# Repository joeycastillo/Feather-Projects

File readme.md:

# Joey's Feather Projects

Finally figured I'd get my hardware hacking efforts under version control. All of these boards are designed to validate under OSH Park's design rules.

Some brief notes on the projects in this repository, in chronological order:

### Unibook Breakout (April 26, 2019)

This barely qualifies as a thing but I'm putting it here anyway for completeness. I wanted to have a simple breakout to four buttons and some signals for an eInk screen and an SD breakout board, to test this ebook idea that I had. No idea how to use EAGLE, I didn't even know what a net was; I just took an Adafruit proto wing, deleted the holes I wasn't using, and used the Name tool to connect some of the holes to some of the other holes, and it basically worked.

Lessons learned: I guess the basics of how to use EAGLE. Also realized that the FeatherWing form factor is so small that OSH Park will make you three of them for $9.

### Hiking Log Rev A (May 16, 2019)

Second board I ever designed: a FeatherWing with spots for an SD card, two environmental sensors (ADT7410 and BME280) and an Ultimate GPS receiver (the old PA6C that Adafruit used to carry; they now stock the PA6H, **which has a different pinout and will not work with this board**). The idea behind this one is you pair it with your favorite Feather, toss it in your backpack and let it log your location and the weather on long hikes.

Lessons learned: the temperature sensor needs to be more thermally isolated from the rest of the board. Also, the temperature readings on the BME280 and ADT7410 tracked each other pretty closely, so I realized I only needed one.

### Hiking Log Rev B (July 10, 2019)

Haven't assembled this one yet (I just ordered it yesterday) but the premise: improve Rev A by streamlining to just the BME280 for temperature, humidity and barometric pressure sensing. Isolate it on a thermal island. Update the GPS to the new [PA6H Ultimate GPS](https://www.adafruit.com/product/790), and add a spot for a flex cable to a [small Sharp Memory Display](https://www.digikey.com/product-detail/en/sharp-microelectronics/LS012B7DD01/425-2900-ND/5054063) so I can see the current conditions. I also added an LED on the Fix pin; not sure if I'll populate it since (hopefully) that data will be on the screen, but it's there as an option.

### E-Book Feather Wing

Rev A is in here but it has some issues. Rev B lives in [its own repository here](https://github.com/joeycastillo/The-Open-Book).

## BOM for these projects

TODO.

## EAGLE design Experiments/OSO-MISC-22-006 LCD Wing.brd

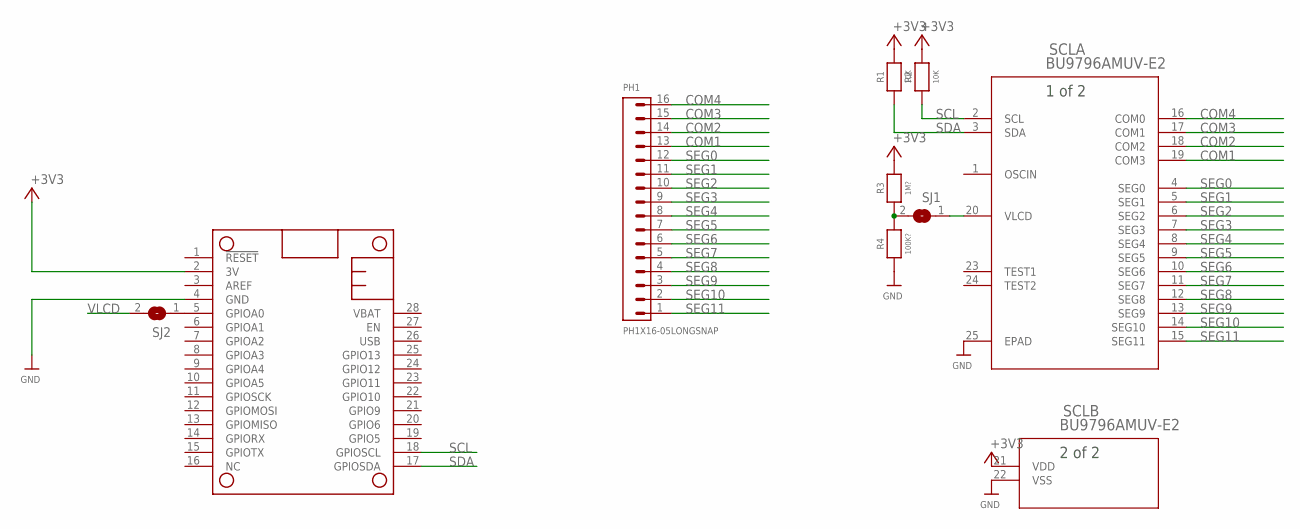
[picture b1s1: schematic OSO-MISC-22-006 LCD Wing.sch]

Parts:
MS1: FEATHERWING
PH1: PH1X16-05LONGSNAP; PHLS005-1-16
R1, R2: 10K; _0805MP
R3: 1M?; _0805MP
R4: 100K?; _0805MP
SCL: BU9796AMUV-E2; VQFN024V4040_ROM
SJ1: SOLDERJUMPERCLOSED; SOLDERJUMPER_CLOSEDWIRE
SJ2: SOLDERJUMPER; SOLDERJUMPER_ARROW_NOPASTE

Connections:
+3V3: MS1.2 (3V), R1.1, R2.1, R3.1, SCL.21 (VDD)
A0: MS1.5 (GPIOA0), SJ2.1
COM1: PH1.13, SCL.19 (COM3)
COM2: PH1.14, SCL.18 (COM2)
COM3: PH1.15, SCL.17 (COM1)
COM4: PH1.16, SCL.16 (COM0)
GND: MS1.4 (GND), R4.2, SCL.22 (VSS), SCL.25 (EPAD)
unnamed: R3.2, R4.1, SJ1.2
SCL: MS1.18 (GPIOSCL), R2.2, SCL.2 (SCL)
SDA: MS1.17 (GPIOSDA), R1.2, SCL.3 (SDA)
SEG0: PH1.12, SCL.4 (SEG0)
SEG1: PH1.11, SCL.5 (SEG1)
SEG2: PH1.10, SCL.6 (SEG2)
SEG3: PH1.9, SCL.7 (SEG3)
SEG4: PH1.8, SCL.8 (SEG4)
SEG5: PH1.7, SCL.9 (SEG5)
SEG6: PH1.6, SCL.10 (SEG6)
SEG7: PH1.5, SCL.11 (SEG7)
SEG8: PH1.4, SCL.12 (SEG8)
SEG9: PH1.3, SCL.13 (SEG9)
SEG10: PH1.2, SCL.14 (SEG10)
SEG11: PH1.1, SCL.15 (SEG11)
VLCD: SCL.20 (VLCD), SJ1.1, SJ2.2

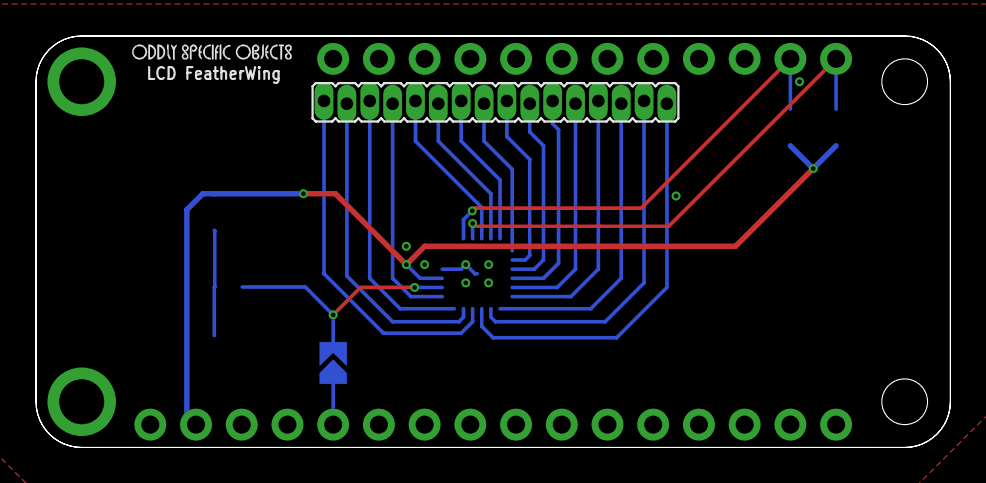
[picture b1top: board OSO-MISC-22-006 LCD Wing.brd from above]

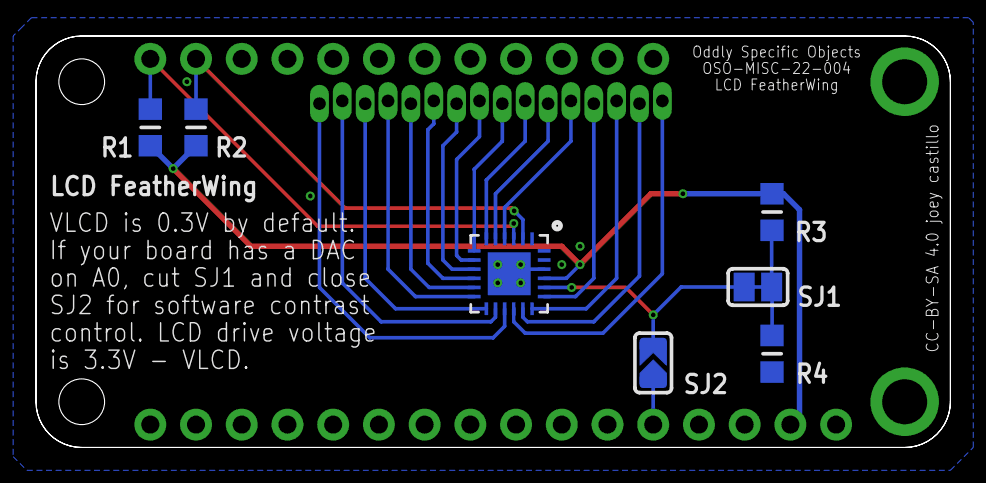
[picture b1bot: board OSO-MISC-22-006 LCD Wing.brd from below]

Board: 2 copper layers, 50.8 x 22.9 mm, 10 parts (7 on the bottom side), 23 nets.

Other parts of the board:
U$2: OSO_WORDMARK_ONELINE_350MIL_1000DPI

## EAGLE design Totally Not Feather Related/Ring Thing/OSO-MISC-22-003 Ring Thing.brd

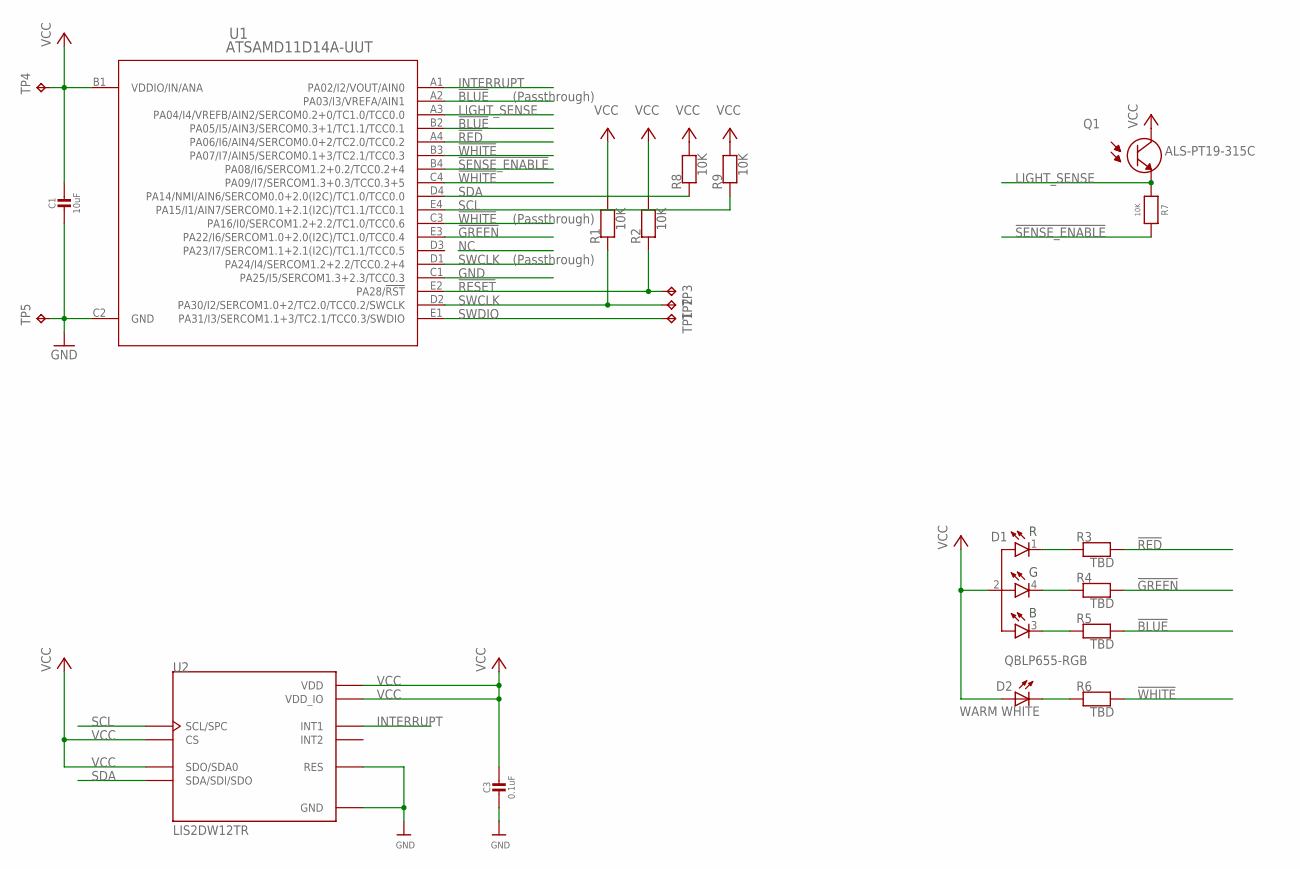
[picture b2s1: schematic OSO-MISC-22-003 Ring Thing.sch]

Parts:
C1: 10uF; _0603MP
C3: 0.1uF; _0402MP
D1: QBLP655-RGB; LED_QBLP655
D2: WARM WHITE; CHIP-LED0603
Q1: ALS-PT19-315C; XDCR_ALS-PT19-315C/L177/TR8
R1, R2, R7, R8, R9: 10K; _0402MP
R3, R4, R5, R6: TBD; _0402MP
TP1, TP2, TP3: TPTP10R; TP10R
TP4: TPTP12SQ; TP12SQ
TP5: TPTP20R; TP20R
U1: ATSAMD11D14A-UUT; WLCSP20_2P4X1P9_MCH
U2: LIS2DW12TR; LGA12R50P4X4_200X200X70

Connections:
!BLUE: R5.2, U1.A2 (PA03/I3/VREFA/AIN1), U1.B2 (PA05/I5/AIN3/SERCOM0.3+1/TC1.1/TCC0.1)
!GREEN: R4.2, U1.E3 (PA22/I6/SERCOM1.0+2.0(I2C)/TC1.0/TCC0.4)
!RED: R3.2, U1.A4 (PA06/I6/AIN4/SERCOM0.0+2/TC2.0/TCC0.2)
!RESET: R2.1, TP3.TP, U1.E2 (PA28/!RST)
!SENSE_ENABLE: R7.2, U1.B4 (PA08/I6/SERCOM1.2+0.2/TCC0.2+4)
!WHITE: R6.2, U1.B3 (PA07/I7/AIN5/SERCOM0.1+3/TC2.1/TCC0.3), U1.C3 (PA16/I0/SERCOM1.2+2.2/TC1.0/TCC0.6), U1.C4 (PA09/I7/SERCOM1.3+0.3/TCC0.3+5)
GND: C1.2, C3.2, TP5.TP, U1.C1 (PA25/I5/SERCOM1.3+2.3/TCC0.3), U1.C2 (GND), U2.6 (GND), U2.7 (RES), U2.8 (GND)
INTERRUPT: U1.A1 (PA02/I2/VOUT/AIN0), U2.12 (INT1)
LIGHT_SENSE: Q1.2 (E), R7.1, U1.A3 (PA04/I4/VREFB/AIN2/SERCOM0.2+0/TC1.0/TC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)
SCL: R9.1, U1.E4 (PA15/I1/AIN7/SERCOM0.1+2.1(I2C)/TC1.1/T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), U2.1 (SCL/SPC)
SDA: R8.1, U1.D4 (PA14/NMI/AIN6/SERCOM0.0+2.0(I2C)/TC1.0/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), U2.4 (SDA/SDI/SDO)
SWCLK: R1.1, TP2.TP, U1.D1 (PA24/I4/SERCOM1.2+2.2/TCC0.2+4), U1.D2 (PA30/I2/SERCOM1.0+2/TC2.0/TCC0.2/SWCLK)
SWDIO: TP1.TP, U1.E1 (PA31/I3/SERCOM1.1+3/TC2.1/TCC0.3/SWDIO)
VCC: C1.1, C3.1, D1.2 (A), D2.A, Q1.1 (C), R1.2, R2.2, R8.2, R9.2, TP4.TP, U1.B1 (VDDIO/IN/ANA), U2.2 (CS), U2.3 (SDO/SDA0), U2.9 (VDD), U2.10 (VDD_IO)
_BLUE: D1.3 (CB), R5.1
_GREEN: D1.4 (CG), R4.1
_RED: D1.1 (CR), R3.1
_WHITE: D2.C, R6.1

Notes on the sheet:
(Passthrough)

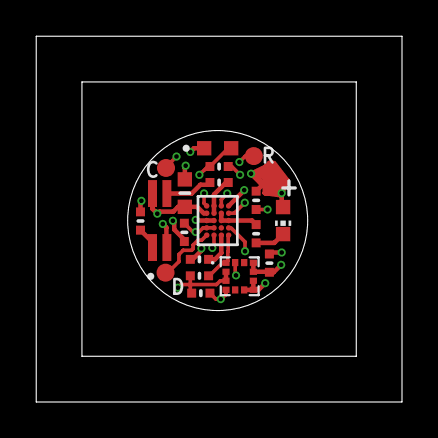
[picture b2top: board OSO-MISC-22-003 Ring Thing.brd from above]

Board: 6 copper layers, 20.3 x 20.3 mm, 21 parts (1 on the bottom side), 18 nets.

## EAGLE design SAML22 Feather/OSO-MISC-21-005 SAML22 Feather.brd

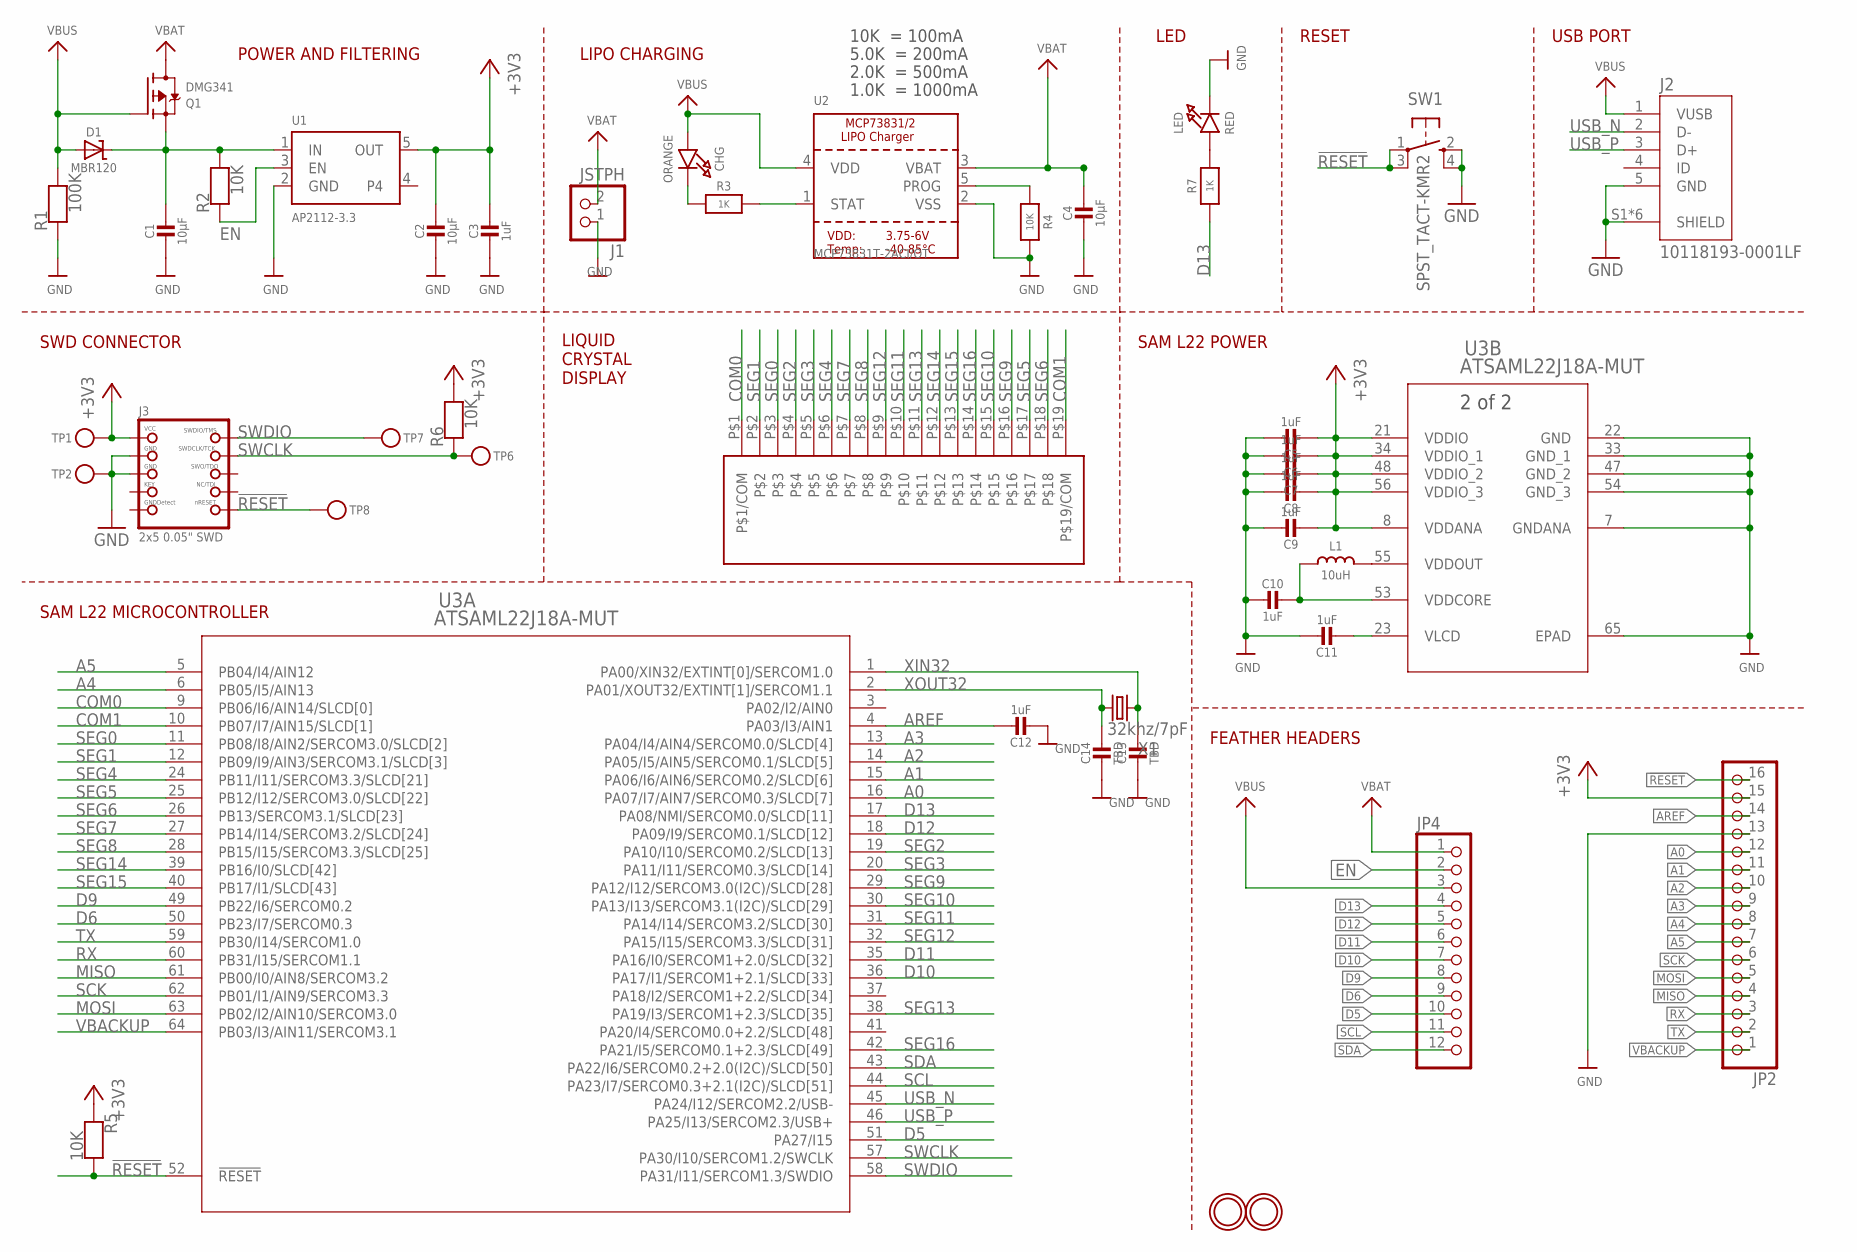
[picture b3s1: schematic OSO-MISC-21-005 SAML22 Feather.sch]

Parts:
C1, C2, C4: 10µF; 0805-NO
C3, C6, C7, C8, C9, C12: 1uF; 0603-NO
C5, C10, C11: 1uF; _0603MP
C13, C14: TBD; _0603MP
CHG: ORANGE; CHIPLED_0805_NOOUTLINE
D1: MBR120; SOD-123
J1: JSTPH; JSTPH2
J2: 10118193-0001LF; FCI_10118193-0001LF
J3: 2x5 0.05" SWD; 2X05_1.27MM_BOX_NOPOSTS
JP2: HEADER-1X16_MIN; 1X16_ROUND_MIN
JP4: HEADER-1X12_MIN; 1X12_ROUND_MIN
L1: 10uH; MICROBUILDER__0805MP
LED: RED; CHIPLED_0805_NOOUTLINE
Q1: DMG341; SOT23-R
R1: 100K; 0603-NO
R2, R4, R5, R6: 10K; 0603-NO
R3, R7: 1K; 0603-NO
SW1: SPST_TACT-KMR2; KMR2
TP1, TP2, TP6, TP7, TP8: TESTPOINTROUND2MMNO; TESTPOINT_ROUND_2MM_NO
U1: AP2112-3.3; SOT23-5
U2: MCP73831T-2ACI/OT; SOT23-5
U3: ATSAML22J18A-MUT; QFN64_9X9MC_MCH
U$6: OD-372
U$31, U$32: MOUNTINGHOLE2.5; MOUNTINGHOLE_2.5_PLATED
X1: 32khz/7pF; XTAL-7015

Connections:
!RESET: J3.10 (NRESET), JP2.16, R5.2, SW1.1, SW1.3 (P1), TP8.P$1, U3.52 (!RESET)
+3V3: C2.1, C3.1, C5.2, C6.2, C7.2, C8.2, C9.2, J3.1 (VCC), JP2.15, R5.1, R6.2, TP1.P$1, U1.5 (OUT), U3.8 (VDDANA), U3.21 (VDDIO), U3.34 (VDDIO_1), U3.48 (VDDIO_2), U3.56 (VDDIO_3)
A0: JP2.12, U3.16 (PA07/I7/AIN7/SERCOM0.3/SLCD[7])
A1: JP2.11, U3.15 (PA06/I6/AIN6/SERCOM0.2/SLCD[6])
A2: JP2.10, U3.14 (PA05/I5/AIN5/SERCOM0.1/SLCD[5])
A3: JP2.9, U3.13 (PA04/I4/AIN4/SERCOM0.0/SLCD[4])
A4: JP2.8, U3.6 (PB05/I5/AIN13)
A5: JP2.7, U3.5 (PB04/I4/AIN12)
AREF: C12.1, JP2.14, U3.4 (PA03/I3/AIN1)
CHG: CHG.C, R3.1
COM0: U3.9 (PB06/I6/AIN14/SLCD[0]), U$6.P$1 (P$1/COM)
COM1: U3.10 (PB07/I7/AIN15/SLCD[1]), U$6.P$19 (P$19/COM)
D5: JP4.10, U3.51 (PA27/I15)
D6: JP4.9, U3.50 (PB23/I7/SERCOM0.3)
D9: JP4.8, U3.49 (PB22/I6/SERCOM0.2)
D10: JP4.7, U3.36 (PA17/I1/SERCOM1+2.1/SLCD[33])
D11: JP4.6, U3.35 (PA16/I0/SERCOM1+2.0/SLCD[32])
D12: JP4.5, U3.18 (PA09/I9/SERCOM0.1/SLCD[12])
D13: JP4.4, R7.1, U3.17 (PA08/NMI/SERCOM0.0/SLCD[11])
EN: JP4.2, R2.1, U1.3 (EN)
GND: C1.2, C2.2, C3.2, C4.2, C5.1, C6.1, C7.1, C8.1, C9.1, C10.2, C11.1, C12.2, C13.2, C14.2, J1.1, J2.5 (GND), J2.S1 (SHIELD), J2.S2 (SHIELD), J2.S3 (SHIELD), J2.S4 (SHIELD), J2.S5 (SHIELD), J2.S6 (SHIELD), J3.3 (GND), J3.5 (GND), JP2.13, LED.C, R1.1, R4.2, SW1.2 (S), SW1.4 (S1), TP2.P$1, U1.2 (GND), U2.2 (VSS), U3.7 (GNDANA), U3.22 (GND), U3.33 (GND_1), U3.47 (GND_2), U3.54 (GND_3), U3.65 (EPAD)
MISO: JP2.4, U3.61 (PB00/I0/AIN8/SERCOM3.2)
MOSI: JP2.5, U3.63 (PB02/I2/AIN10/SERCOM3.0)
unnamed: LED.A, R7.2
PROG: R4.1, U2.5 (PROG)
RX: JP2.3, U3.60 (PB31/I15/SERCOM1.1)
SCK: JP2.6, U3.62 (PB01/I1/AIN9/SERCOM3.3)
SCL: JP4.11, U3.44 (PA23/I7/SERCOM0.3+2.1(I2C)/SLCD[51])
SDA: JP4.12, U3.43 (PA22/I6/SERCOM0.2+2.0(I2C)/SLCD[50])
SEG0: U3.11 (PB08/I8/AIN2/SERCOM3.0/SLCD[2]), U$6.P$3
SEG1: U3.12 (PB09/I9/AIN3/SERCOM3.1/SLCD[3]), U$6.P$2
SEG2: U3.19 (PA10/I10/SERCOM0.2/SLCD[13]), U$6.P$4
SEG3: U3.20 (PA11/I11/SERCOM0.3/SLCD[14]), U$6.P$5
SEG4: U3.24 (PB11/I11/SERCOM3.3/SLCD[21]), U$6.P$6
SEG5: U3.25 (PB12/I12/SERCOM3.0/SLCD[22]), U$6.P$17
SEG6: U3.26 (PB13/SERCOM3.1/SLCD[23]), U$6.P$18
SEG7: U3.27 (PB14/I14/SERCOM3.2/SLCD[24]), U$6.P$7
SEG8: U3.28 (PB15/I15/SERCOM3.3/SLCD[25]), U$6.P$8
SEG9: U3.29 (PA12/I12/SERCOM3.0(I2C)/SLCD[28]), U$6.P$16
SEG10: U3.30 (PA13/I13/SERCOM3.1(I2C)/SLCD[29]), U$6.P$15
SEG11: U3.31 (PA14/I14/SERCOM3.2/SLCD[30]), U$6.P$10
SEG12: U3.32 (PA15/I15/SERCOM3.3/SLCD[31]), U$6.P$9
SEG13: U3.38 (PA19/I3/SERCOM1+2.3/SLCD[35]), U$6.P$11
SEG14: U3.39 (PB16/I0/SLCD[42]), U$6.P$12
SEG15: U3.40 (PB17/I1/SLCD[43]), U$6.P$13
SEG16: U3.42 (PA21/I5/SERCOM0.1+2.3/SLCD[49]), U$6.P$14
STAT: R3.2, U2.1 (STAT)
SWCLK: J3.4 (SWDCLK), R6.1, TP6.P$1, U3.57 (PA30/I10/SERCOM1.2/SWCLK)
SWDIO: J3.2 (SWDIO), TP7.P$1, U3.58 (PA31/I11/SERCOM1.3/SWDIO)
TX: JP2.2, U3.59 (PB30/I14/SERCOM1.0)
USB_N: J2.2 (D-), U3.45 (PA24/I12/SERCOM2.2/USB-)
USB_P: J2.3 (D+), U3.46 (PA25/I13/SERCOM2.3/USB+)
VBACKUP: JP2.1, U3.64 (PB03/I3/AIN11/SERCOM3.1)
VBAT: C4.1, J1.2, JP4.1, Q1.3 (D), U2.3 (VBAT)
VBUS: CHG.A, D1.A, J2.1 (VUSB), JP4.3, Q1.1 (G), R1.2, U2.4 (VDD)
VDDCORE: C10.1, L1.1, U3.53 (VDDCORE)
VDDOUT: L1.2, U3.55 (VDDOUT)
VHI: C1.1, D1.C, Q1.2 (S), R2.2, U1.1 (IN)
VLCD: C11.2, U3.23 (VLCD)
XIN32: C13.1, U3.1 (PA00/XIN32/EXTINT[0]/SERCOM1.0), X1.4 (2)
XOUT32: C14.1, U3.2 (PA01/XOUT32/EXTINT[1]/SERCOM1.1), X1.1

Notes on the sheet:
LIPO CHARGING
LED
RESET
POWER AND FILTERING
10K = 100mA
5.0K = 200mA
2.0K = 500mA
1.0K = 1000mA
FEATHER HEADERS
USB PORT
SAM L22 POWER
SAM L22 MICROCONTROLLER
SWD CONNECTOR
LIQUID CRYSTAL DISPLAY

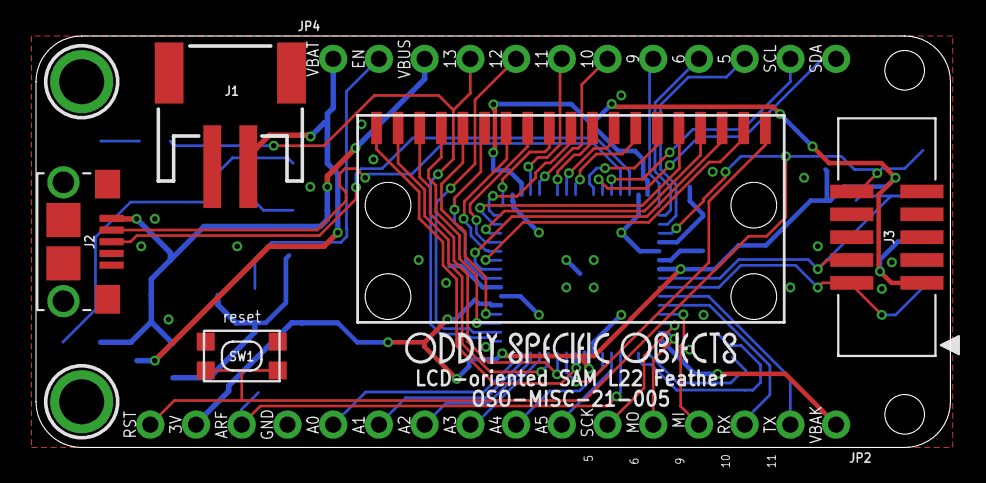
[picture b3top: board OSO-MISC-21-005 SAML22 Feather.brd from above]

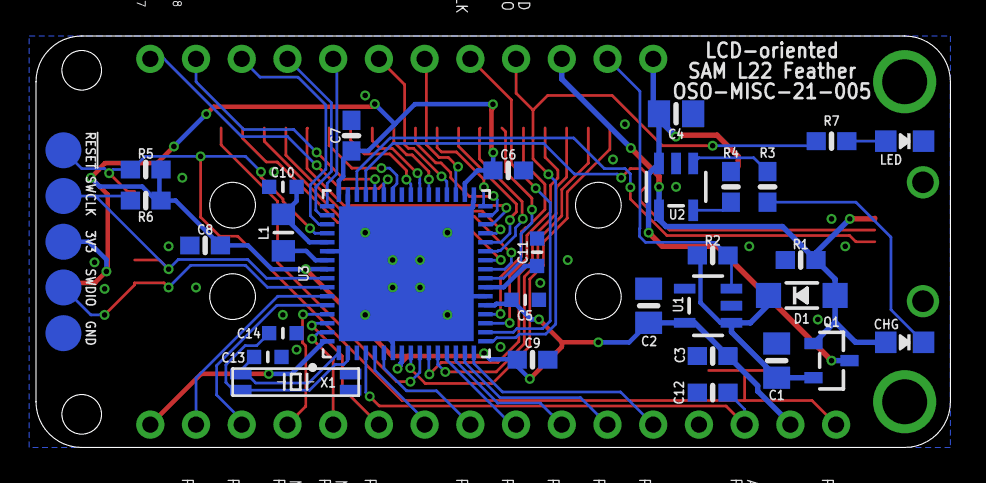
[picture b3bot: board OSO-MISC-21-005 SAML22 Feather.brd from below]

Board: 2 copper layers, 50.8 x 22.9 mm, 46 parts (36 on the bottom side), 61 nets.

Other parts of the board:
U$12: OSO_WORDMARK_ONELINE_350MIL_1000DPI
U$13: OSO_WORDMARK_ONELINE_725MIL_1000DPI

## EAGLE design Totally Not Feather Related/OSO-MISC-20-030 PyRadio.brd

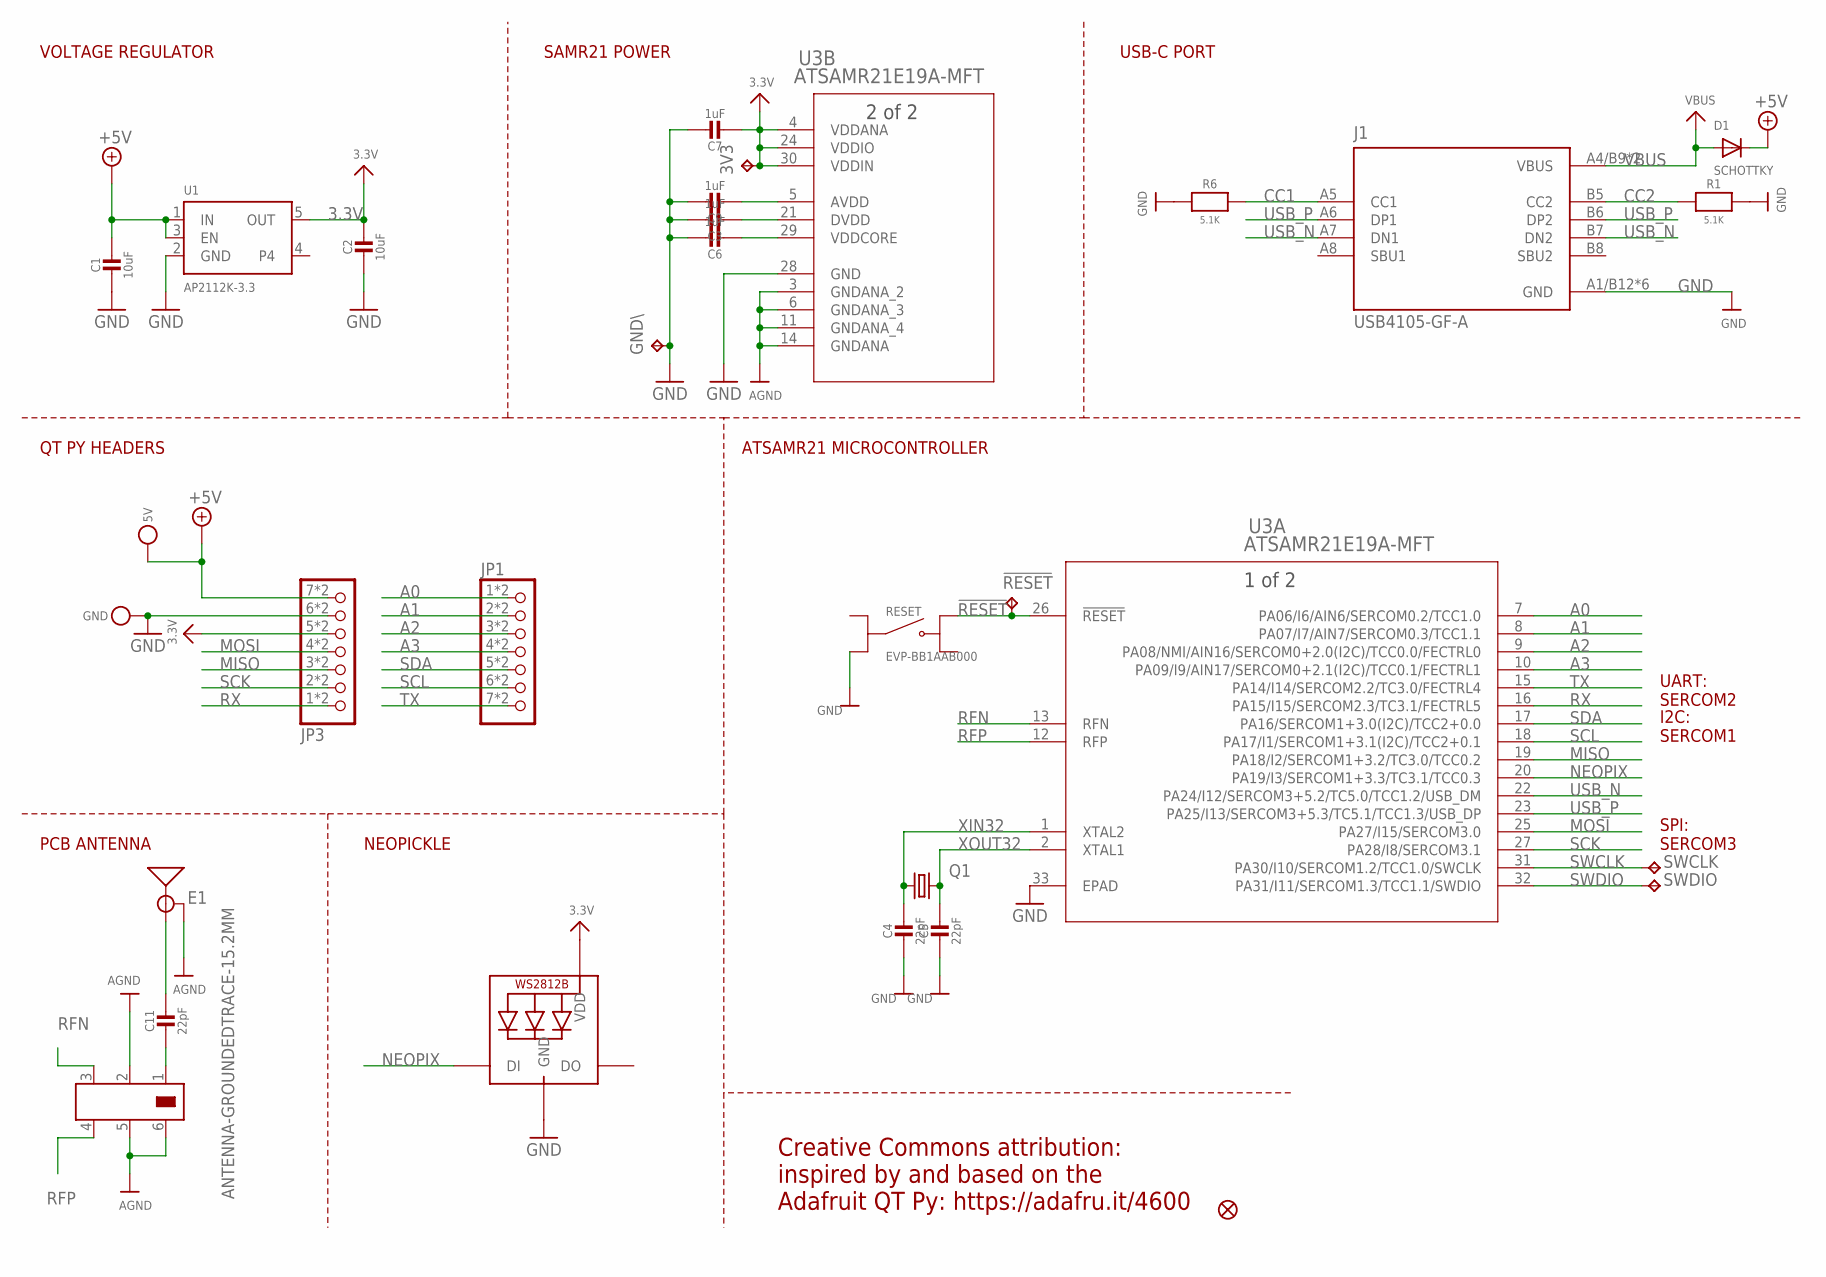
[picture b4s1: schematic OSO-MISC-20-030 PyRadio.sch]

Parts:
3V3: TPTP20R; TP20R
5V: TESTPOINT_1X3; TESTPOINT_RECT_1X3MM
!RESET: TPTP20R; TP20R
BALUN: JOHANSON_2450BM15A0015E; 0805_BALUN
C1, C2: 10uF; _0603MP
C3, C6, C7, C9: 1uF; _0603MP
C4, C5, C11: 22pF; _0603MP
D1: SCHOTTKY; SOD-323F
E1: ANTENNA-GROUNDEDTRACE-15.2MM; TRACE_ANTENNA_2.4GHZ_15.2MM
GND: TESTPOINT_1X3; TESTPOINT_RECT_1X3MM
GND\: TPTP20R; TP20R
J1: USB4105-GF-A; GCT_USB4105-GF-A
JP1, JP3: HEADER-1X7_CASTEL; 1X07_CASTEL
LED: WS2812B_SK6805_1515; SK6805_1515
Q1: KX-7; 3.2X2.5_KX-7
R1, R6: 5.1K; _0603MP
RESET: EVP-BB1AAB000; SW_EVP-BB1AAB000
SWCLK: TPTP20R; TP20R
SWDIO: TPTP20R; TP20R
U1: AP2112K-3.3; SOT23-5
U3: ATSAMR21E19A-MFT; QFN32_5X5MC_MCH
U$8: FIDUCIAL_1MM

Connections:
3.3V: 3V3.TP, C2.1, C7.2, JP3.5, JP3.5C (5), LED.2 (VDD), U1.5 (OUT), U3.4 (VDDANA), U3.24 (VDDIO), U3.30 (VDDIN)
!RESET: !RESET.TP, RESET.B1, U3.26 (!RESET)
+5V: 5V.P$1, C1.1, D1.C, JP3.7, JP3.7C (7), U1.1 (IN), U1.3 (EN)
A0: JP1.1, JP1.1C (1), U3.7 (PA06/I6/AIN6/SERCOM0.2/TCC1.0)
A1: JP1.2, JP1.2C (2), U3.8 (PA07/I7/AIN7/SERCOM0.3/TCC1.1)
A2: JP1.3, JP1.3C (3), U3.9 (PA08/NMI/AIN16/SERCOM0+2.0(I2C)/TCC0.0/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)
A3: JP1.4, JP1.4C (4), U3.10 (PA09/I9/AIN17/SERCOM0+2.1(I2C)/TCC0.1/F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)
AGND: BALUN.2, BALUN.5, BALUN.6, E1.GND, U3.3 (GNDANA_2), U3.6 (GNDANA_3), U3.11 (GNDANA_4), U3.14 (GNDANA)
ANT_OUT: BALUN.1, C11.2
AVDD: C9.2, U3.5 (AVDD)
CC1: J1.A5 (CC1), R6.2
CC2: J1.B5 (CC2), R1.1
DVDD: C3.2, U3.21 (DVDD)
GND: C1.2, C2.2, C3.1, C4.2, C5.2, C6.1, C7.1, C9.1, GND.P$1, GND\.TP, J1.A1/B12 (GND), J1.B1/A12 (GND), J1.G1 (GND), J1.G2 (GND), J1.G3 (GND), J1.G4 (GND), JP3.6, JP3.6C (6), LED.4 (GND), R1.2, R6.1, RESET.A2, U1.2 (GND), U3.28 (GND), U3.33 (EPAD)
MISO: JP3.3, JP3.3C (3), U3.19 (PA18/I2/SERCOM1+3.2/TC3.0/TCC0.2)
MOSI: JP3.4, JP3.4C (4), U3.25 (PA27/I15/SERCOM3.0)
NEOPIX: LED.1 (DI), U3.20 (PA19/I3/SERCOM1+3.3/TC3.1/TCC0.3)
PCB_ANT: C11.1, E1.ANT (SIGNAL)
RFN: BALUN.3, U3.13 (RFN)
RFP: BALUN.4, U3.12 (RFP)
RX: JP3.1, JP3.1C (1), U3.16 (PA15/I15/SERCOM2.3/TC3.1/FECTRL5)
SCK: JP3.2, JP3.2C (2), U3.27 (PA28/I8/SERCOM3.1)
SCL: JP1.6, JP1.6C (6), U3.18 (PA17/I1/SERCOM1+3.1(I2C)/TCC2+0.1)
SDA: JP1.5, JP1.5C (5), U3.17 (PA16/SERCOM1+3.0(I2C)/TCC2+0.0)
SWCLK: SWCLK.TP, U3.31 (PA30/I10/SERCOM1.2/TCC1.0/SWCLK)
SWDIO: SWDIO.TP, U3.32 (PA31/I11/SERCOM1.3/TCC1.1/SWDIO)
TX: JP1.7, JP1.7C (7), U3.15 (PA14/I14/SERCOM2.2/TC3.0/FECTRL4)
USB_N: J1.A7 (DN1), J1.B7 (DN2), U3.22 (PA24/I12/SERCOM3+5.2/TC5.0/TCC1.2/USB_DM)
USB_P: J1.A6 (DP1), J1.B6 (DP2), U3.23 (PA25/I13/SERCOM3+5.3/TC5.1/TCC1.3/USB_DP)
VBUS: D1.A, J1.A4/B9 (VBUS), J1.B4/A9 (VBUS)
VDDCORE: C6.2, U3.29 (VDDCORE)
XIN32: C4.1, Q1.1, U3.1 (XTAL2)
XOUT32: C5.1, Q1.3 (2), U3.2 (XTAL1)

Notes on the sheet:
Creative Commons attribution: inspired by and based on the Adafruit QT Py: https://adafru.it/4600
UART: SERCOM2
I2C: SERCOM1
SPI: SERCOM3
VOLTAGE REGULATOR
SAMR21 POWER
USB-C PORT
ATSAMR21 MICROCONTROLLER
QT PY HEADERS
PCB ANTENNA
NEOPICKLE

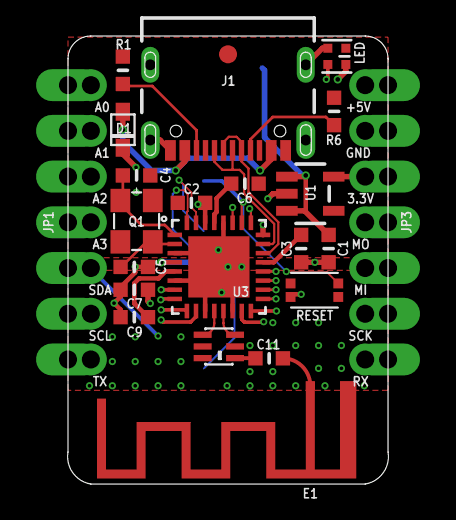
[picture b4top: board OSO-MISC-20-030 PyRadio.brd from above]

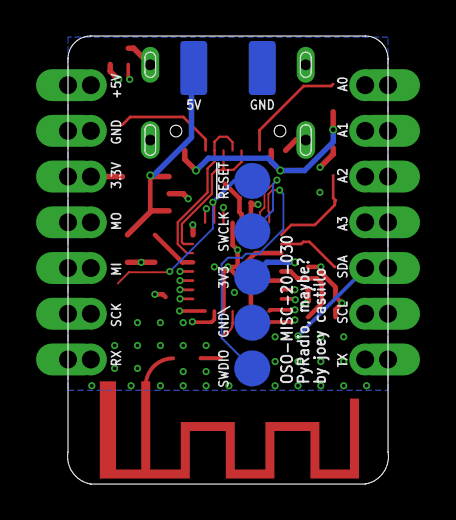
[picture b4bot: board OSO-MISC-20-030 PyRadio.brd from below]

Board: 6 copper layers, 17.8 x 24.9 mm, 30 parts (7 on the bottom side), 33 nets.

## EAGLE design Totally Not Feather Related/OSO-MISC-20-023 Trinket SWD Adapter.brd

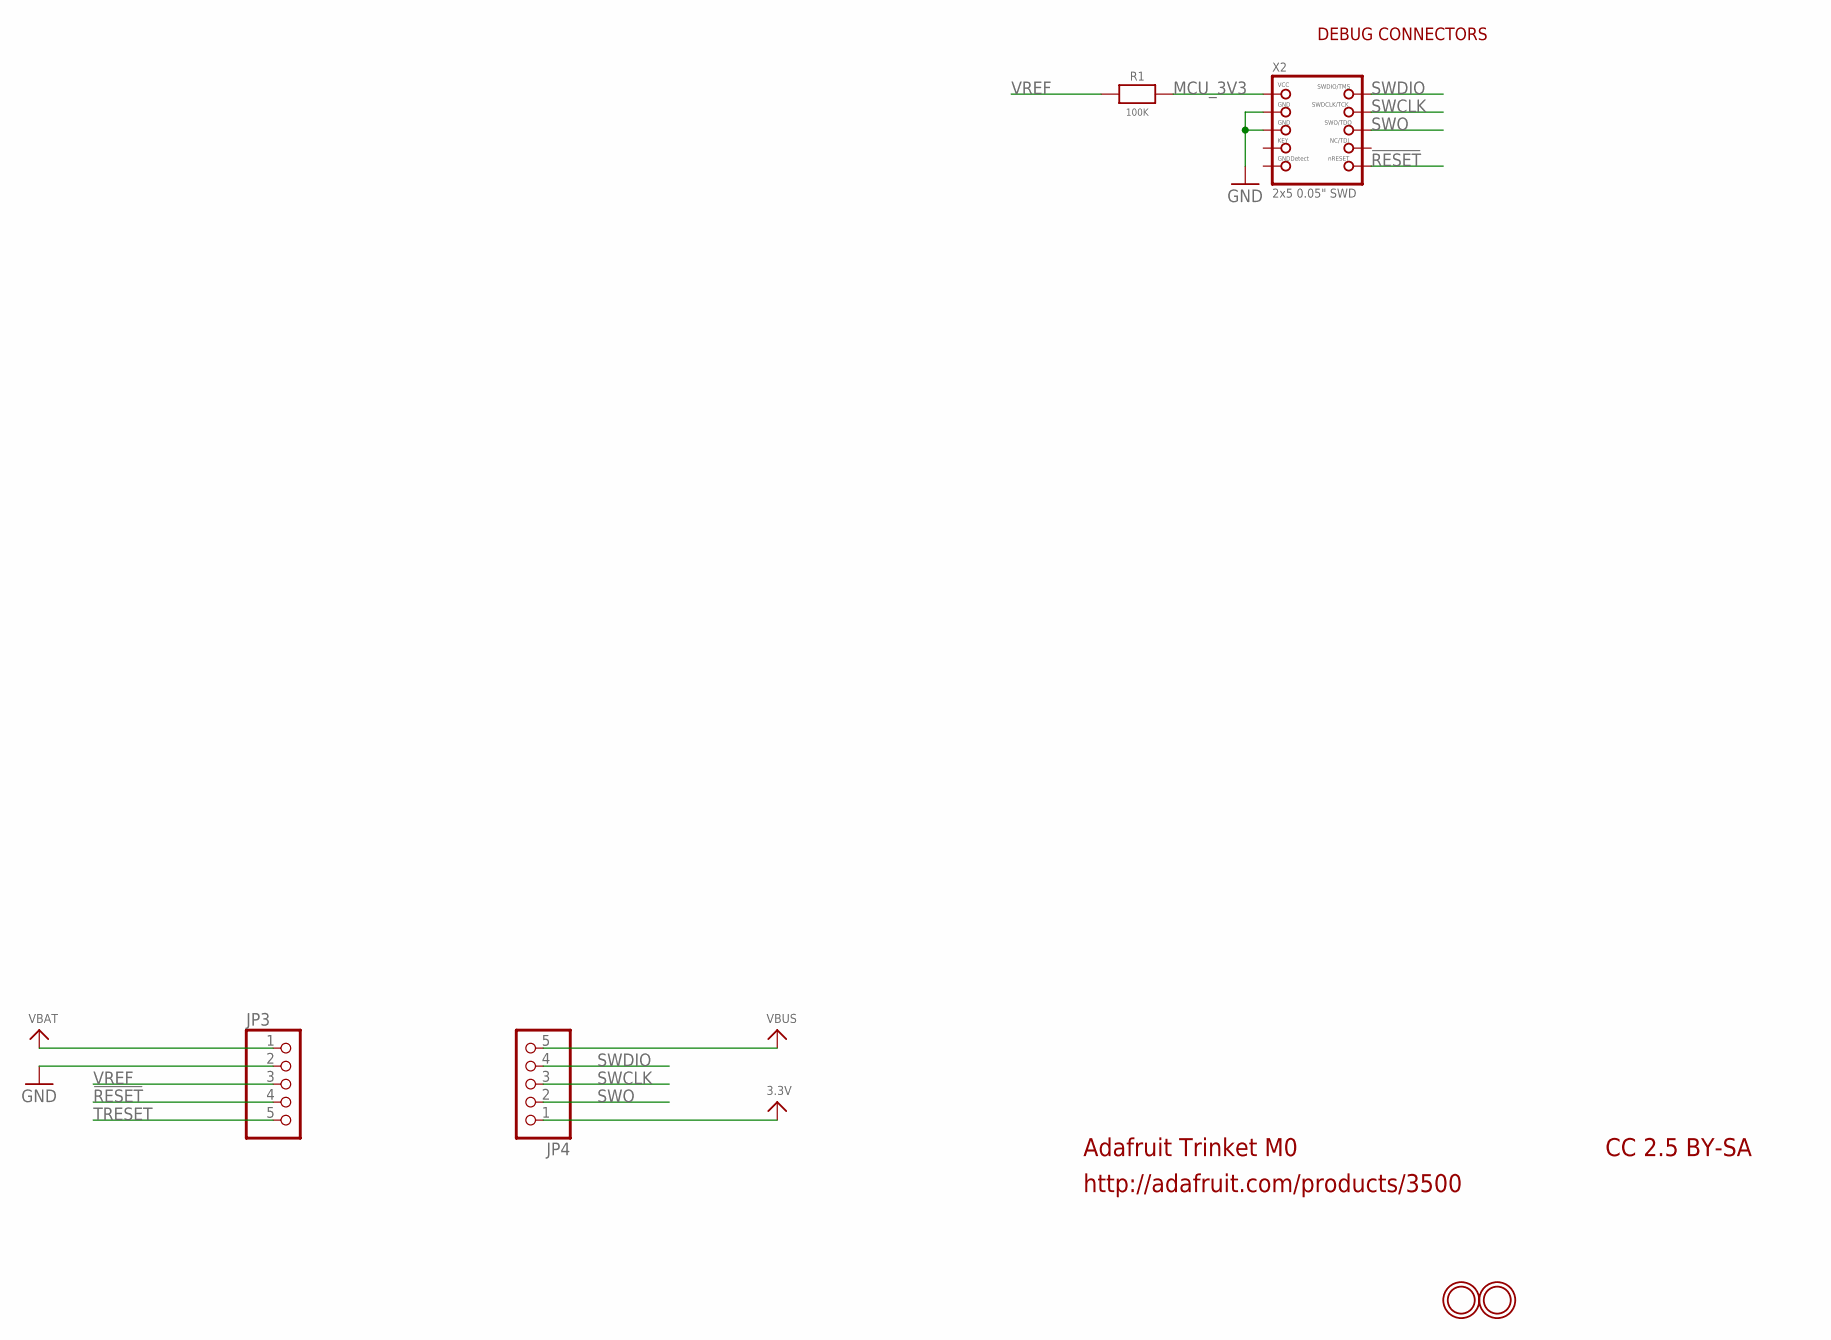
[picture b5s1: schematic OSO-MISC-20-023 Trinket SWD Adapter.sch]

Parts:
JP3, JP4: HEADER-1X576MIL; 1X05_ROUND_76
R1: 100K; 0805-NO
U$8, U$9: MOUNTINGHOLE2.0; MOUNTINGHOLE_2.0_PLATED
X2: 2x5 0.05" SWD; 2X05_1.27MM_BOX_POSTS

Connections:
3.3V: JP4.1
!RESET: JP3.4, X2.10 (NRESET)
GND: JP3.2, X2.3 (GND), X2.5 (GND)
MCU_3V3: R1.2, X2.1 (VCC)
SWCLK: JP4.3, X2.4 (SWDCLK)
SWDIO: JP4.4, X2.2 (SWDIO)
SWO: JP4.2, X2.6 (SWO)
TRESET: JP3.5
VBAT: JP3.1
VBUS: JP4.5
VREF: JP3.3, R1.1

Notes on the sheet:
Adafruit Trinket M0
http://adafruit.com/products/3500
CC 2.5 BY-SA
DEBUG CONNECTORS

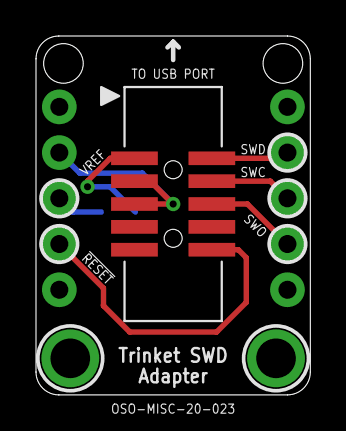
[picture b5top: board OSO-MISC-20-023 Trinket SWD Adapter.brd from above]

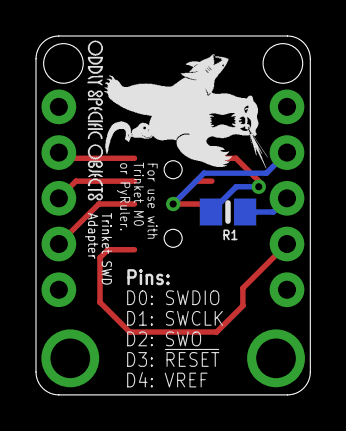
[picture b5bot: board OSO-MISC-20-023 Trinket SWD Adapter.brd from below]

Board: 2 copper layers, 15.2 x 19.9 mm, 8 parts (3 on the bottom side), 7 nets.

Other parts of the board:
U$1: OSO_BEAR_250X360MIL_1000DPI
U$2: OSO_WORDMARK_ONELINE_350MIL_1000DPI

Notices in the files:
Experiments/EPD Research/OSO-MISC-20-017 Parallel E-Paper Test Board 2.brd:
CC-BY-SA 4.0
Experiments/OSO-MISC-22-006 LCD Wing.brd:
CC-BY-SA 4.0 joey castillo
Totally Not Feather Related/OSO-MISC-20-018 Memory Gadget.brd:
CC-BY-SA 4.0, whatever it is
parts and their libraries:
microbuilder: This work is placed in the public domain, and may be freely used for commercial and non-commercial work with the following conditions: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
COPYRIGHT: Copyright (C) 2022 Ultra Librarian. All rights reserved.
COPYRIGHT: Copyright (C) 2018 Accelerated Designs. All rights reserved
